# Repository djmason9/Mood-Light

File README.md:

Arduino Mood-Light V2.1
==========

The controller is based off the ATMega88p. You can get parts on Ebay cheap (I paid $10 for 6 micro controllers) and they are great!

PARTS
- Power Converter
- ATMEL ATMega88p
- Common Anode RGB LED
- 100ohm -120ohm 0805 SMD Resistor
- Power Switch
- 6mm Momentary Switch
- 2.1mm SMD Barrel Plug

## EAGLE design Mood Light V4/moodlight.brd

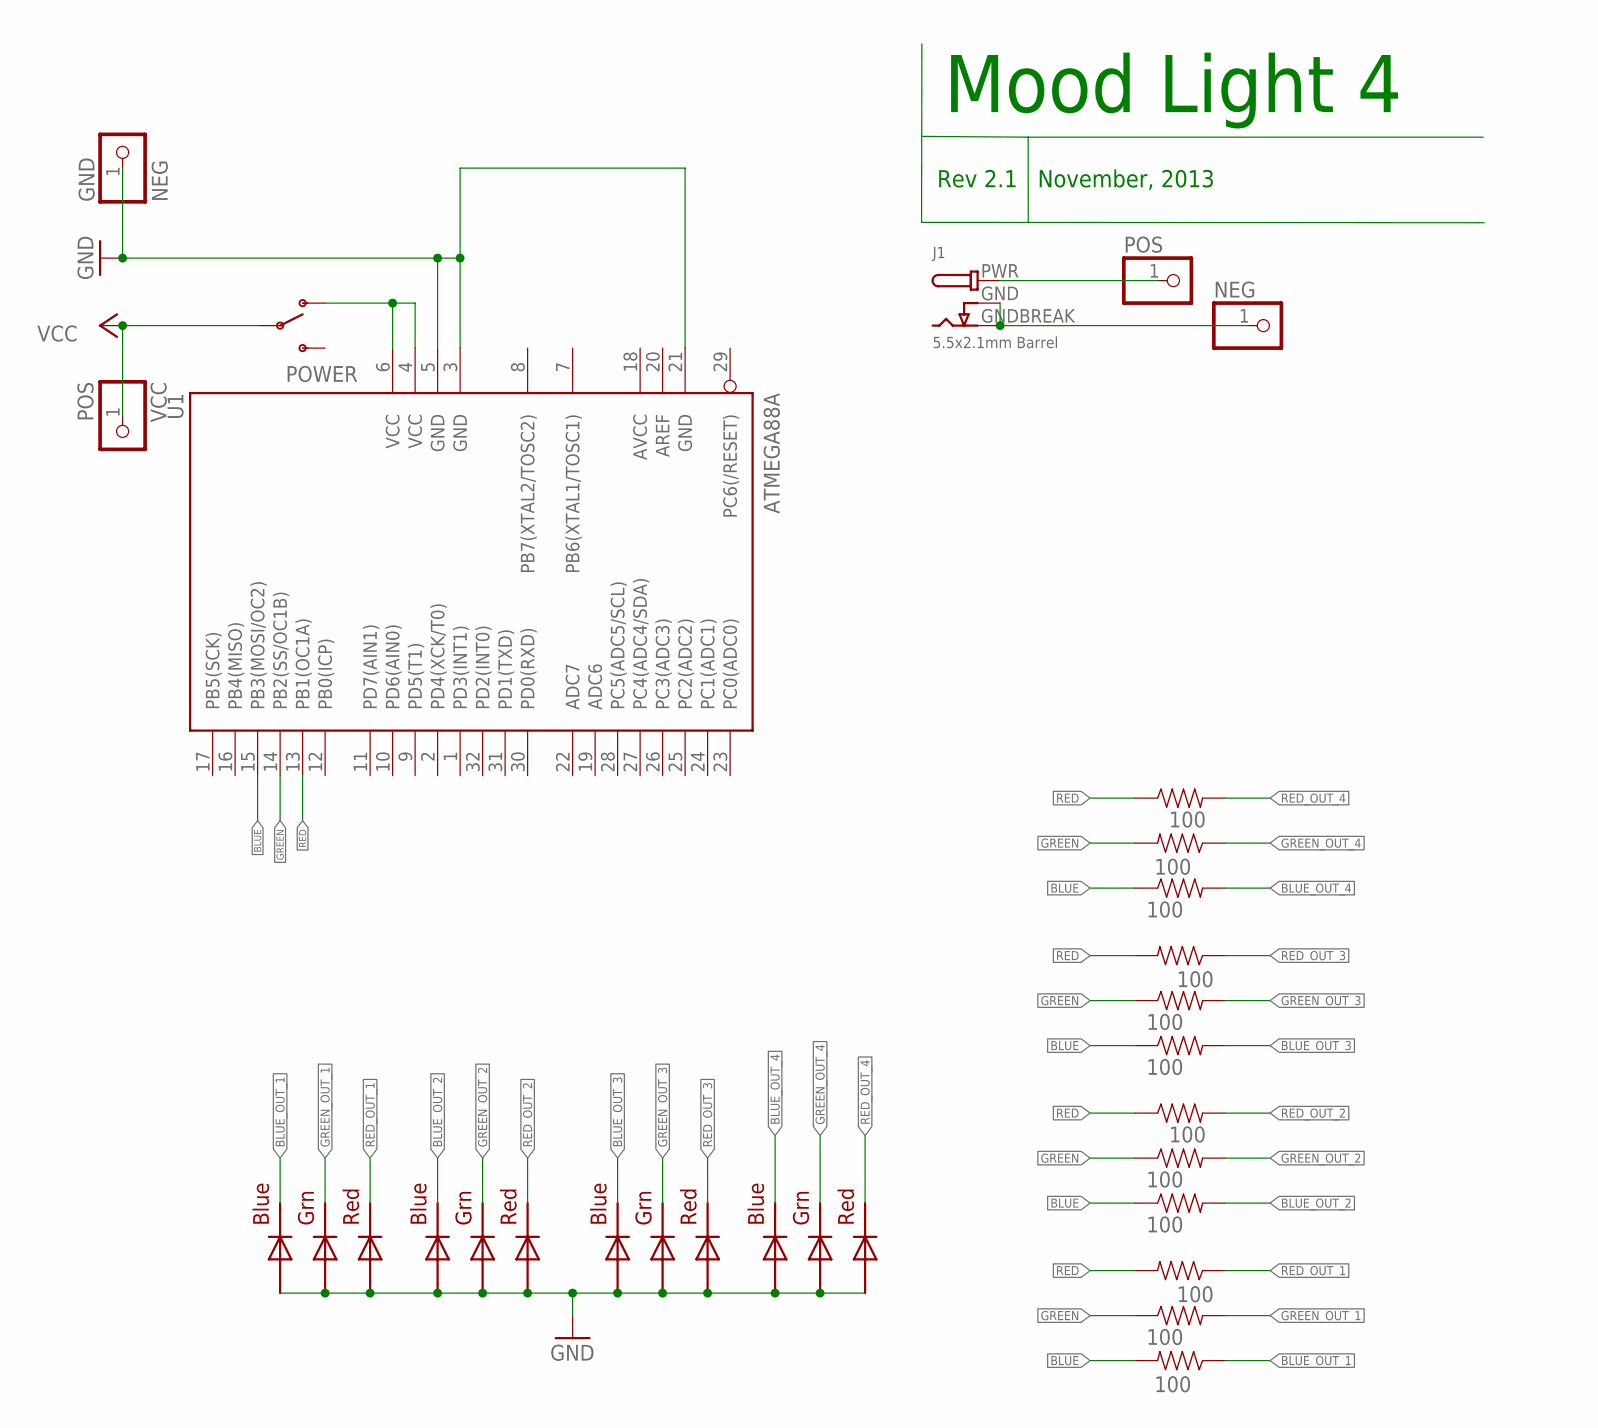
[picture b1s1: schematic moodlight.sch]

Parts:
GND: NEG; 1X01
J1: 5.5x2.1mm Barrel; DCJACK_2MM_SMT
LED1, LED2, LED3, LED4: RGBLED5050
NEG: PINHD-1X1; 1X01
POS: PINHD-1X1; 1X01
POWER: 5V; SWITCH-SPDT
R1, R2, R3, R4, R5, R6, R7, R8, R9, R10, R11, R12: 100; 0603-RES
U1: ATMEGA88A; TQFP32-08
VCC: POS; 1X01

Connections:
AVCC: U1.18 (AVCC)
BLUE: R3.1, R6.1, R9.1, R12.2, U1.15 (PB3(MOSI/OC2))
BLUE_OUT_1: LED1.4 (BLUE_C), R12.1
BLUE_OUT_2: LED2.4 (BLUE_C), R9.2
BLUE_OUT_3: LED3.4 (BLUE_C), R6.2
BLUE_OUT_4: LED4.4 (BLUE_C), R3.2
GND: GND.1, LED1.1 (GREEN_A), LED1.2 (RED_A), LED1.3 (BLUE_A), LED2.1 (GREEN_A), LED2.2 (RED_A), LED2.3 (BLUE_A), LED3.1 (GREEN_A), LED3.2 (RED_A), LED3.3 (BLUE_A), LED4.1 (GREEN_A), LED4.2 (RED_A), LED4.3 (BLUE_A), U1.3 (GND), U1.5 (GND), U1.21 (GND)
GREEN: R2.2, R5.1, R8.1, R11.1, U1.14 (PB2(SS/OC1B))
GREEN_OUT_1: LED1.6 (GREEN_C), R11.2
GREEN_OUT_2: LED2.6 (GREEN_C), R8.2
GREEN_OUT_3: LED3.6 (GREEN_C), R5.2
GREEN_OUT_4: LED4.6 (GREEN_C), R2.1
unnamed: POWER.1 (O), U1.4 (VCC), U1.6 (VCC)
unnamed: J1.PWR, POS.1
unnamed: J1.GND (GNDBREAK), J1.GNDBREAK (GND), NEG.1
RED: R1.1, R4.2, R7.1, R10.2, U1.13 (PB1(OC1A))
RED_OUT_1: LED1.5 (RED_C), R10.1
RED_OUT_2: LED2.5 (RED_C), R7.2
RED_OUT_3: LED3.5 (RED_C), R4.1
RED_OUT_4: LED4.5 (RED_C), R1.2
VCC: POWER.2, VCC.1

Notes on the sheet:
Mood Light 4
Rev 2.1 November, 2013

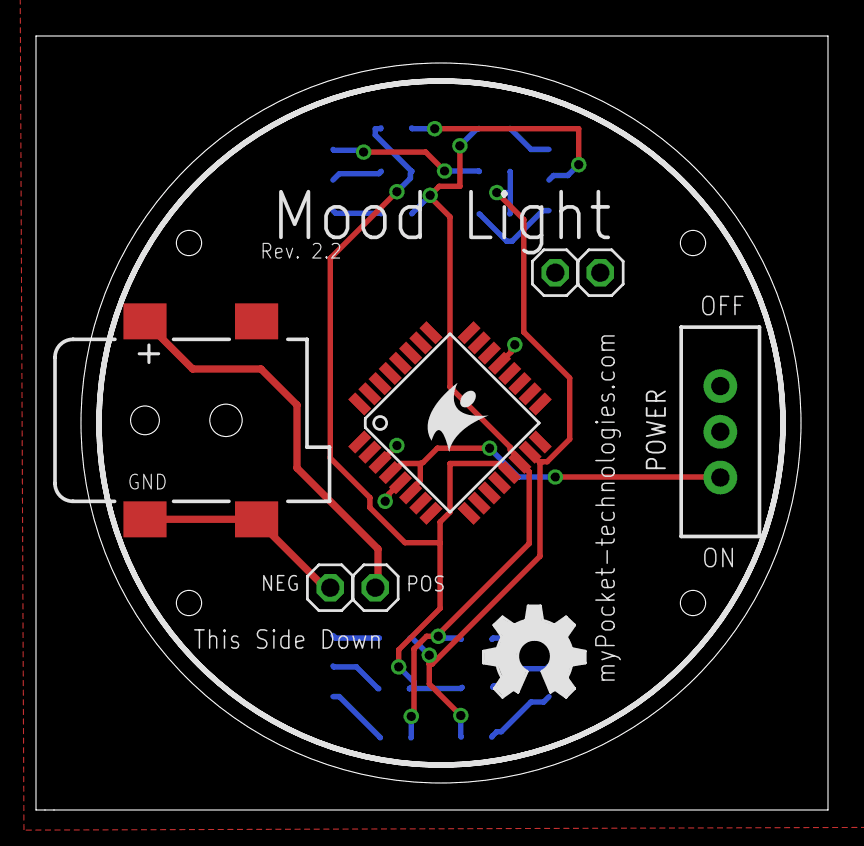
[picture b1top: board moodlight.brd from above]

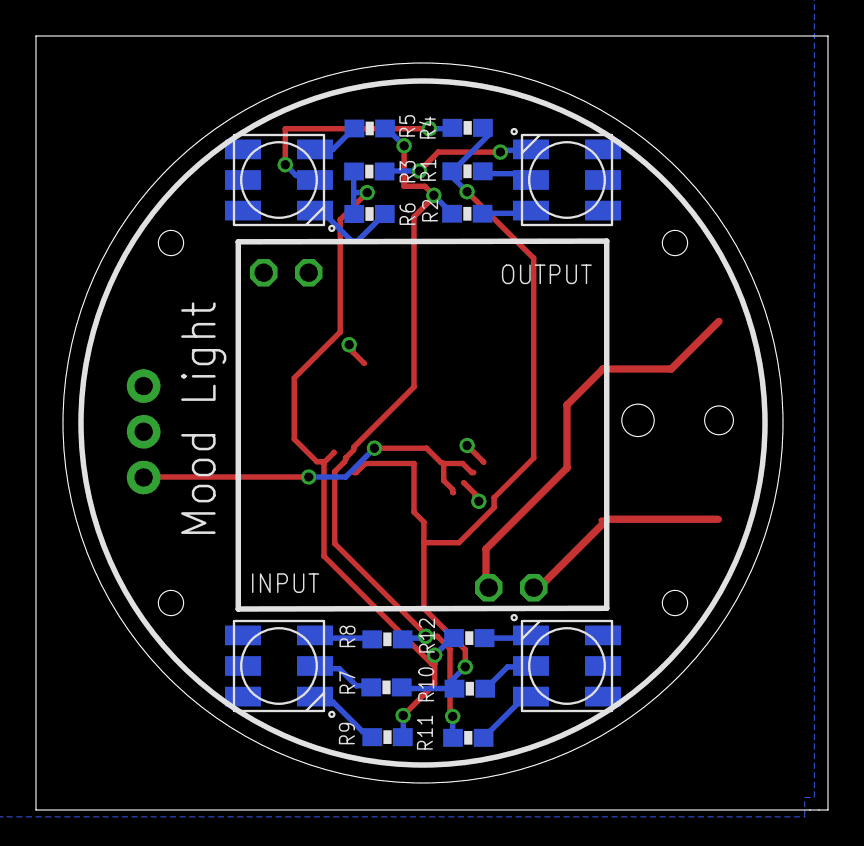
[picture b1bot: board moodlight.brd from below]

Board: 2 copper layers, 44.0 x 43.0 mm, 25 parts (16 on the bottom side), 20 nets.

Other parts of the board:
U$1: OSHW_FILLX200_NOTEXT
U$2: MYPOCKETLOGO_SM

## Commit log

2013-12-13 added moodlight3
2014-07-19 not sure

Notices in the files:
parts and their libraries:
SparkFun-Electromechanical: Licensing: CC v3.0 Share-Alike You are welcome to use this library for commercial purposes.
